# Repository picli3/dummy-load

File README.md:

# dummy-load

Carga electrónica o dummy load basada en **LM358** y MOSFET, pensada para probar fuentes de alimentación y convertidores bajo condiciones controladas.

## Propósito del proyecto
Este diseño permite aplicar una carga artificial a una fuente o etapa DC para evaluar regulación, calentamiento, respuesta y comportamiento general sin depender de una carga real fija.

## Qué incluye
- esquemático de la carga electrónica
- PCB en KiCad
- base práctica para laboratorio, pruebas y validación de fuentes

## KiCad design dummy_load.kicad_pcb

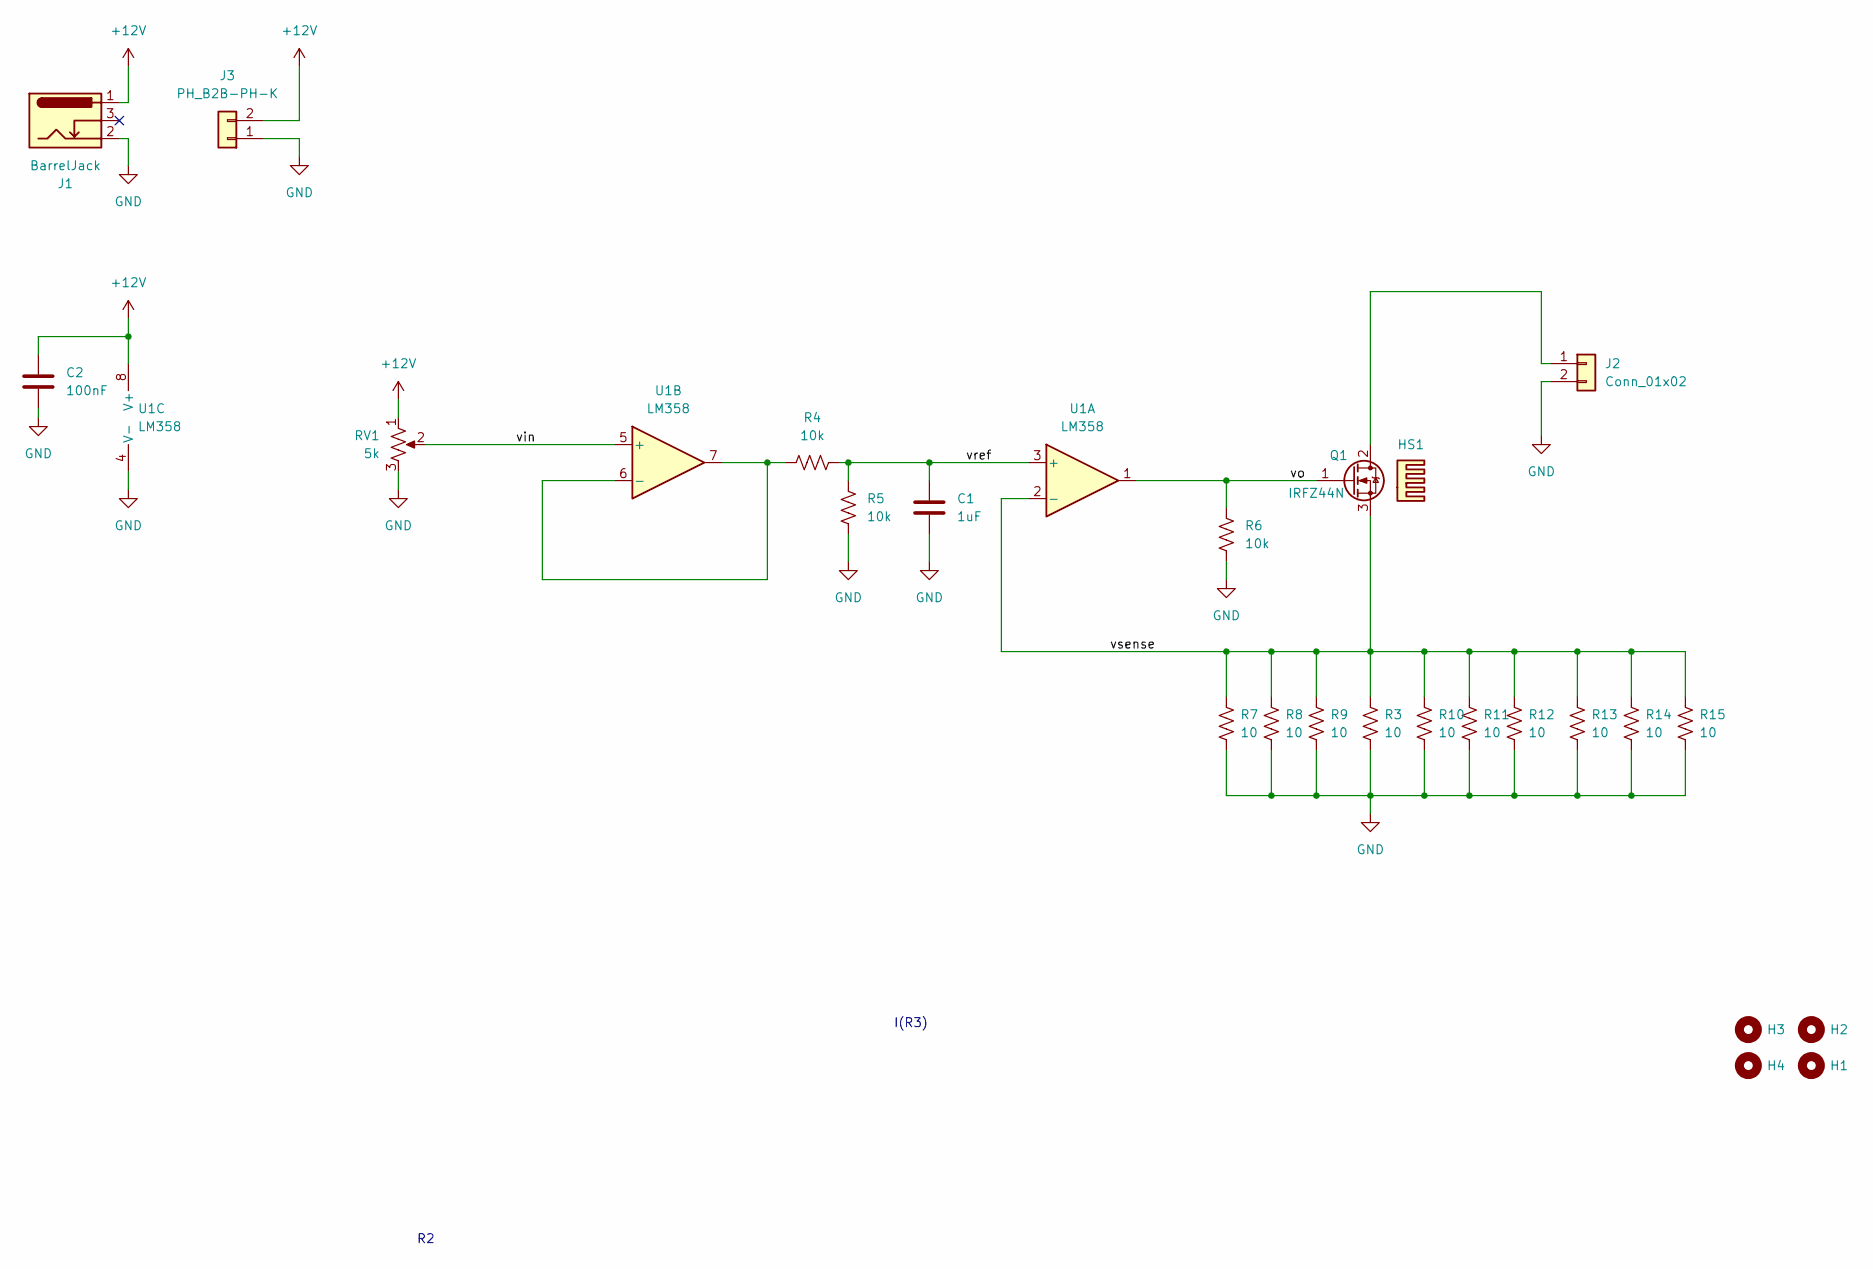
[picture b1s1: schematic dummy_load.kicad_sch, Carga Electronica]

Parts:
C1: 1uF; C_Disc_D5.0mm_W2.5mm_P5.00mm
C2: 100nF; C_Disc_D5.0mm_W2.5mm_P2.50mm
H1, H2, H3, H4: MountingHole; MountingHole_3.2mm_M3_Pad_Via
HS1: Heatsink; disipador_VGA
J1: BarrelJack; BarrelJack_Horizontal
J2: Conn_01x02; TerminalBlock_Phoenix_MKDS-1,5-2-5.08_1x02_P5.08mm_Horizont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
J3: PH_B2B-PH-K; JST_PH_B2B-PH-K_1x02_P2.00mm_Vertical
Q1: IRFZ44N; TO-220-3_Horizontal_TabUp
R3, R7, R8, R9, R10, R11, R12, R13, R14, R15: 10; R_Axial_DIN0414_L11.9mm_D4.5mm_P15.24mm_Horizontal
R4, R5, R6: 10k; R_Axial_DIN0207_L6.3mm_D2.5mm_P10.16mm_Horizontal
RV1: 5k; Potentiometer_Alps_RK09Y11_Single_Horizontal
U1: LM358; DIP-8_W7.62mm_Socket

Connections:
+12V: C2.1, J1.1, J3.2, RV1.1, U1.8 (V+)
/vin: RV1.2, U1.5 (+)
/vo: Q1.1 (G), R6.2, U1.1
/vref: C1.1, R4.1, R5.1, U1.3 (+)
/vsense: Q1.3 (S), R3.1, R7.1, R8.1, R9.1, R10.1, R11.1, R12.1, R13.1, R14.1, R15.1, U1.2 (-)
GND: C1.2, C2.2, J1.2, J2.2, J3.1, R3.2, R5.2, R6.1, R7.2, R8.2, R9.2, R10.2, R11.2, R12.2, R13.2, R14.2, R15.2, RV1.3, U1.4 (V-)
unnamed: J2.1, Q1.2 (D)
unnamed: R4.2, U1.6 (-), U1.7

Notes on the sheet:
I(R3)

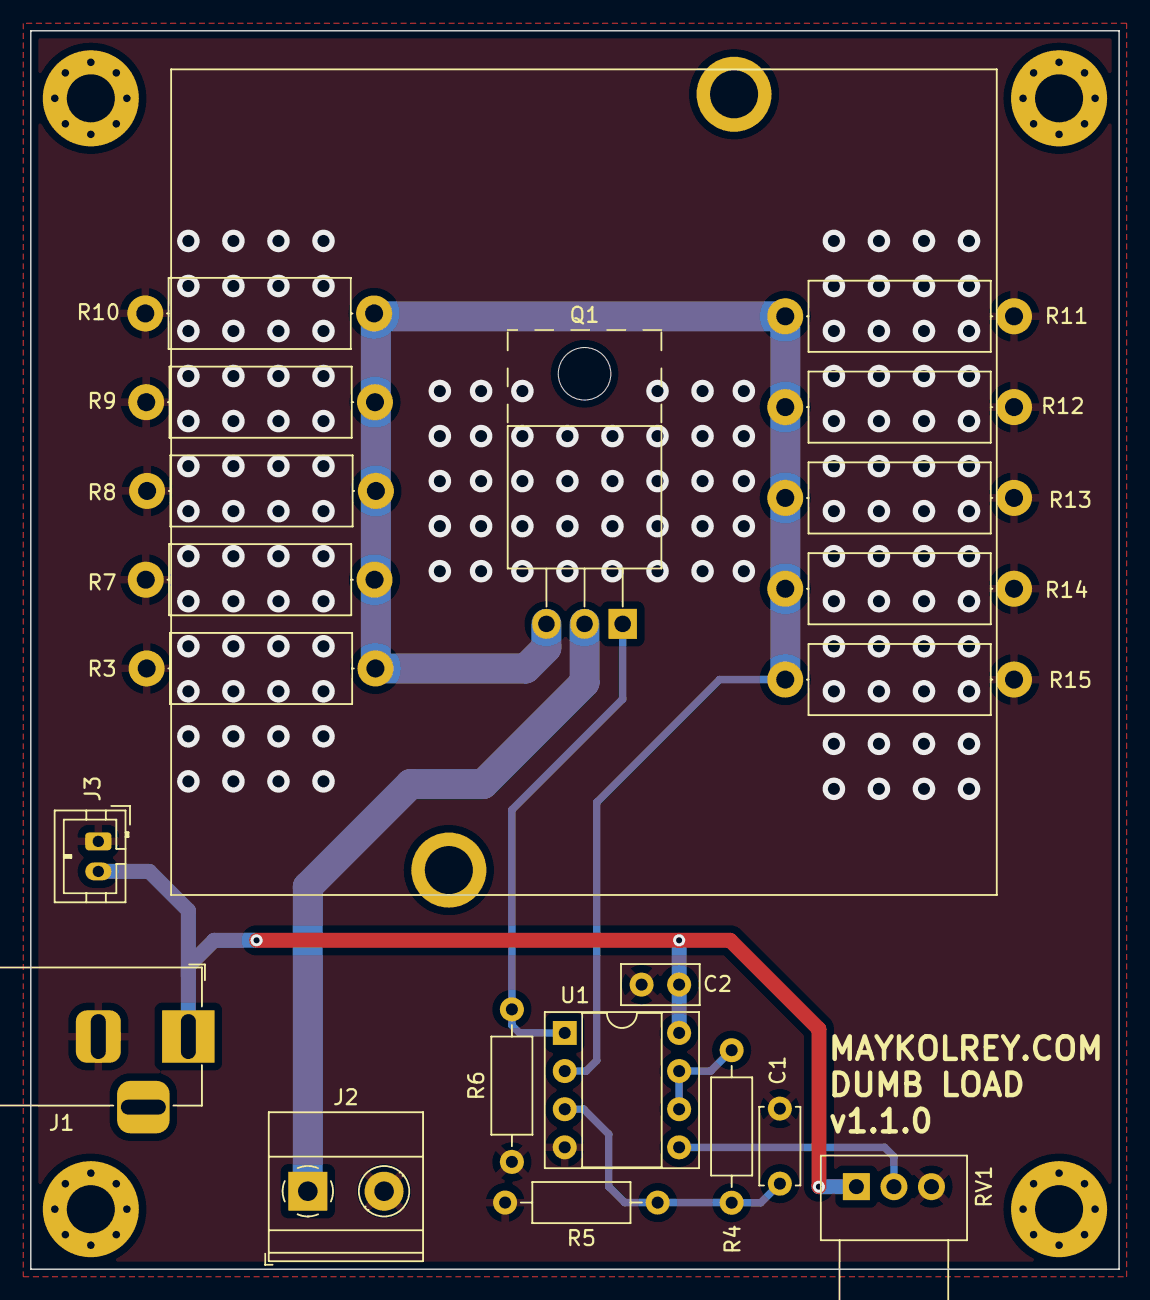
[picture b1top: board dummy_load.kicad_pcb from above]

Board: 2 copper layers, 72.5 x 82.5 mm, 26 parts (0 on the bottom side), 8 nets.

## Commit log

2023-11-27 dummy load TL082
2023-11-29 version con LM358 (SIMULACION)
2024-07-22 Completada la version 1
2024-08-24 corrigiendo footprint del disipador de calor
2024-08-25 creando archivos de fabricación
2024-08-27 corrigiendo el conector jack-DC invertido
2026-04-29 Agrega README con descripción inicial del proyecto
2026-04-29 Mejora README con descripción específica del proyecto
